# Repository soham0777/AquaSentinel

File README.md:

<div align="center">

**[Website](https://soham0777.github.io/AquaSentinel/)** · **[Live dashboard](https://aquasentinel-live.web.app)** · **[Pitch film](docs/media/aquasentinel-pitch-film.mp4)** · **[Journey film](docs/media/aquasentinel-journey-film.mp4)** · **[Finale deck](01_PITCH_20Nov/02_Pitch_Deck_7min_AS_SUBMITTED_17Nov.pdf)** · **[Drawings](04_R3_FULL_SIZE_DESIGN/04_Drawings/AquaSentinel_R3_Drawing_Set.pdf)** · **[Cost sheet](08_COST_AND_BUSINESS/04_AquaSentinel_Cost_48k_Value_Engineered.pdf)**

</div>

---

## 🏆 Encouragement Award, AAKRUTI 2026 India Finale

On **20 November 2026**, at the India Finale of the 16th **AAKRUTI Innovation Competition** by **Dassault Systèmes** (DS Campus, Pune), **AquaSentinel received an Encouragement Award**. The competition drew more than 15,000 students in 2,443 teams. **Sanjivani University** also received an **Outstanding College Participation** award.

<p align="center">

<br><sub>Left: our team presenting AquaSentinel at the India Finale. Right: finalists, jury and organisers. Photos: Dassault Systèmes Solutions Lab, from <a href="https://www.linkedin.com/posts/aakrutiinnovationcompetition2026-3dexperienceworld2027-ugcPost-7529524580290416640-ub56/">the official results post</a>.</sub>
</p>

> 🌟 **Encouragement Awards:** Sanjivani's Hero, **AquaSentinel**, SANJIVANI UNIVERSITY
> <br><sub>From the organisers' results post, <a href="https://www.linkedin.com/posts/aakrutiinnovationcompetition2026-3dexperienceworld2027-ugcPost-7529524580290416640-ub56/">Dassault Systèmes Solutions Lab on LinkedIn</a>. Also reported by <a href="https://www.punekarnews.in/indian-students-win-dassault-systemes-aakruti-2026-with-healthcare-innovations/">Punekar News</a>, 20 Nov 2026.</sub>

Jury: Lalit Kumar Das, Sudhir Patil, Aditi Singh, Ravikiran Pothukuchi and Suchit Jain.

---

## The problem, in four numbers

| | |
|---:|---|
| **1.4 million** | people die every year from unsafe drinking water, sanitation and hygiene (WHO, 2023) |
| **2 lakh** | Indians die every year for lack of safe water (NITI Aayog, 2018) |
| **296** | polluted river stretches and locations in India; **54** in Maharashtra, the most of any state (CPCB, 2025) |
| **once a month** | how often most river monitoring points are sampled, by hand. A spill lasts a few hours. |

On the Godavari at Kopargaon, a spill at two in the morning looks like water. By sunrise it has moved on, and nobody was there to take the sample.

## Our answer

> **AquaSentinel rides a guide pole on a bridge pier, reads the water every 15 minutes, and when the river changes it lights a red beacon, raises an SMS alert and bottles a sample of that water, at that minute, for the lab.**

```mermaid
flowchart LR
    R(["River"]) --> S["7 sensors<br/>pH · TDS · turbidity · water temp<br/>air temp + humidity · light · MQ-3"]
    S --> N["Arduino Nano<br/>on our milled Sensor Hub"]
    N -- "USB · one line a second" --> P["Raspberry Pi<br/>141 lines of decision rules"]
    P --> B{"Normal for<br/>this river?"}
    B -- yes --> L["Log · green light"]
    B -- "2 of 3 readings unusual" --> A["Red beacon · SMS alert<br/>pump fills the sample bottle"]
```

## Watch it

<table>
<tr>
<td width="50%" align="center"><br><b>The pitch</b> · 92 s<br><sub>The problem, the float, how it works and what it costs.</sub></td>
<td width="50%" align="center"><br><b>Our journey</b> · 92 s<br><sub>From our first handwritten page to the board we milled, and what we learned.</sub></td>
</tr>
</table>

<sub>Both films are made only from our own CAD, renders, drawings, dashboard captures and sourced figures. The milling shot is drawn from our real isolation G-code.</sub>

## Pour something in

The 1:5 LIVE model on our table carries the real, full-size sensors in a dish of water. Change the water and it names what it sees.

| Put this in the dish | It says | Because |
|---|---|---|
| Clean tap water | 🟢 **NORMAL** | readings stay where it learned them |
| A spoon of salt | 🔴 **INDUSTRIAL** | dissolved solids jump |
| A little vinegar | 🔴 **ACIDIC** | pH falls |
| A spoon of soil | 🔴 **RUNOFF** | the water turns cloudy while the salts stay flat |
| Sanitiser held at the bottle | 🔴 **SOLVENT** | vapour above the sample |
| Pull out the temperature probe | 🔴 **SENSOR FAULT** (blinking) | a dead sensor is never reported as clean water |

It learns the dish for 20 seconds first, and needs two unusual readings out of three before it calls anything.

<p align="center"><br><sub>The Raspberry Pi's dashboard after a spoon of salt, captured from the simulator built into our software.</sub></p>

## The board we milled

- **Why:** ten small boards on a tray clashed twice in SOLIDWORKS, so we drew one board instead.
- **What:** Sensor Hub v1.2, 104 × 72 mm, single-sided, drawn in KiCad, milled on a desktop CNC on **12 November**.
- **How:** an Arduino Nano reads all seven sensors and drives the light and the pump; every sensor has its own labelled header.
- **Learned:** Windows blocked the usual milling program, so we wrote our own G-code sender. The TDS board disturbs the pH probe, so the Nano powers it only while it reads.
- **Tested:** on **13 November** all seven sensors, the beacon and the pump answered through the board.

<br clear="right">

## The full-size float, R3

<p align="center"> <br><sub>Left: the R3 at dusk, rendered in 3DEXCITE Creative Experience on the 3DEXPERIENCE platform. Right: the float follows the river through 2 m of rise.</sub></p>

| | |
|---|---|
| **Assembly** | 66 part numbers, 144 parts, 48.5 kg, one SOLIDWORKS assembly |
| **Structure** | 316L pole and pier brackets, 6061 aluminium frame, rotomoulded PE hulls |
| **Motion** | rides a 2-inch pole on eight rollers through 2 m of river rise; turns with the current like a weathervane |
| **Design checks** | **14 of 14 pass**: reserve buoyancy 2.27, freeboard 143 mm, righting arm positive to 60° |
| **Guide pole** | 64.0 MPa with pinned ends and the carriage couple: safety factor **2.66** on 170 MPa |
| **CAD caught** | the pole running through the electronics pod, and a mass of 48.5 kg, not the 25.4 kg we guessed |

### Six SOLIDWORKS drawings

<p align="center">  <br><sub>AS3-DWG-01 to 06, A3, first-angle: installation, float, guide carriage, sensor well, hull, pier bracket. Native <code>.SLDDRW</code> files in <a href="04_R3_FULL_SIZE_DESIGN/04_Drawings/SOLIDWORKS">04_Drawings/SOLIDWORKS</a>.</sub></p>

## How we got here

```mermaid
timeline
    title AquaSentinel, 2026
    Idea : One page of ideas, called AquaRight then
    Design : The R3 in SOLIDWORKS : CAD stops us twice
    5 Oct : FDC submitted : pole and bracket simulated
    31 Oct : 1:5 LIVE model designed around the real sensors
    7 Nov : Assembly manuals
    12 Nov : Sensor Hub milled with our own G-code sender
    13 Nov : All seven sensors answer through the board
    19–20 Nov : India Geo Finale, DS Campus, Pune : Encouragement Award
```

## What it costs

| | |
|---|---|
| One sentinel at 100 units | **₹47,886** before GST |
| The first one | ₹64,616 |
| One real-time monitoring station | ₹35–40 lakh, the price of **73–84** sentinels |
| Proposed service | ₹8,000 a month; hardware paid back in about 12 months |

Costed from Indian supplier listings, November 2026, line by line in [the cost sheet](08_COST_AND_BUSINESS/04_AquaSentinel_Cost_48k_Value_Engineered.pdf).

## Run the software, no hardware needed

```bash
cd 07_RASPBERRY_PI_SOFTWARE/aquasentinel
python3 -m aquasentinel --simulate     # dashboard on http://localhost:8080, plays the six waters
python3 tools/self_test.py             # checks the decision rules on every water
```

On the Raspberry Pi, `bash install.sh` sets up the service, the SIM800L port and the full-screen dashboard. See [PI_SETUP_AND_OPERATION.md](07_RASPBERRY_PI_SOFTWARE/aquasentinel/PI_SETUP_AND_OPERATION.md).

## Inside this repository

| Folder | What you will find |
|---|---|
| [`01_PITCH_20Nov`](01_PITCH_20Nov) | the 7-minute finale deck (PPTX + PDF), the final pitch script, a one-page glance card, the mechanical and design Q&A, and the fact check behind every number |
| [`02_FILMS`](02_FILMS) | the pitch film and the journey film (both have music), and the team's raw recordings |
| [`03_BOOTH_PRINTS`](03_BOOTH_PRINTS) | every booth print: A1 poster, 12 A3 story boards, drawings, leave-behind, part tags, "Try me" stickers, bottle labels, with the print order sheet |
| [`04_R3_FULL_SIZE_DESIGN`](04_R3_FULL_SIZE_DESIGN) | R3 assembly manual, parts list, Pack and Go, native SOLIDWORKS parts, six drawings, 14 design checks, renders, STEP for every part, and the pole and bracket FEA |
| [`05_LIVE_MODEL_1to5`](05_LIVE_MODEL_1to5) | the 1:5 LIVE model: 31-page assembly manual, 38 STL print files, SOLIDWORKS parts and assembly |
| [`06_ELECTRONICS_AND_PCB`](06_ELECTRONICS_AND_PCB) | electronics manual, Sensor Hub v1.2 KiCad design, G-code, our G-code sender, Nano firmware |
| [`07_RASPBERRY_PI_SOFTWARE`](07_RASPBERRY_PI_SOFTWARE) | decision rules, dashboard, SMS, Firebase cloud, logging, installer, self-test |
| [`08_COST_AND_BUSINESS`](08_COST_AND_BUSINESS) | the cost summary, the full working and the cost sheet |
| [`09_CREATIVE_EXPERIENCE_3DEXCITE`](09_CREATIVE_EXPERIENCE_3DEXCITE) | 3DEXCITE storyline, assets and renders, AR model, story video |
| [`10_SUBMISSIONS_AND_CERTIFICATES`](10_SUBMISSIONS_AND_CERTIFICATES) | every stage we submitted, the FDC report and the participation certificates |
| [`11_PROJECT_RECORDS_AND_AUDITS`](11_PROJECT_RECORDS_AND_AUDITS) | audits, reorganisation and purge reports, the backup policy |
| [`docs`](docs) | the project website, the films and every image on this page |

New here? Start with [`00_START_HERE.md`](00_START_HERE.md).

## Where it stands

| Proven | Not yet |
|---|---|
| All 7 sensors, the beacon and the pump work through our own board (13 Nov) | an SMS received end to end |
| The Raspberry Pi reads the board live; pH, turbidity and MQ-3 calibrated | the 1:5 model floated in water |
| The [live cloud dashboard](https://aquasentinel-live.web.app) shows the Kopargaon 1:5 station (18 Nov) | the full-size R3 built: it is a design, checked in CAD |
| R3: 14 of 14 design checks, 2 SOLIDWORKS Simulation studies | a tank test, then 30 days on the Godavari |

## The team

**Built by**

| | |
|---|---|
| **Soham Prabhakar Kadu** | Team leader and project lead · Third Year, AI & ML |
| **Bhakti Ajay Kadam** | Electronics lead, finale presenter · Third Year, Computer Science & Engineering |

**Team Sanjivani Hero's Journey** also included Prasad Satish Ugale (Direct Second Year, Mechanical Engineering) and Tanmay Nilesh Pendbhaje (First Year, Mechanical Engineering), with Dr. Kiran Wakchaure as mentor.

AG26-1500$41 · Sanjivani University, Kopargaon · AAKRUTI Innovation Competition 2026 by Dassault Systèmes

<sub>Code and documentation are under the MIT licence; the presentation, films, renders and drawings are the team's copyright. Award photos are © Dassault Systèmes, shown with credit. See [LICENSE](LICENSE).</sub>

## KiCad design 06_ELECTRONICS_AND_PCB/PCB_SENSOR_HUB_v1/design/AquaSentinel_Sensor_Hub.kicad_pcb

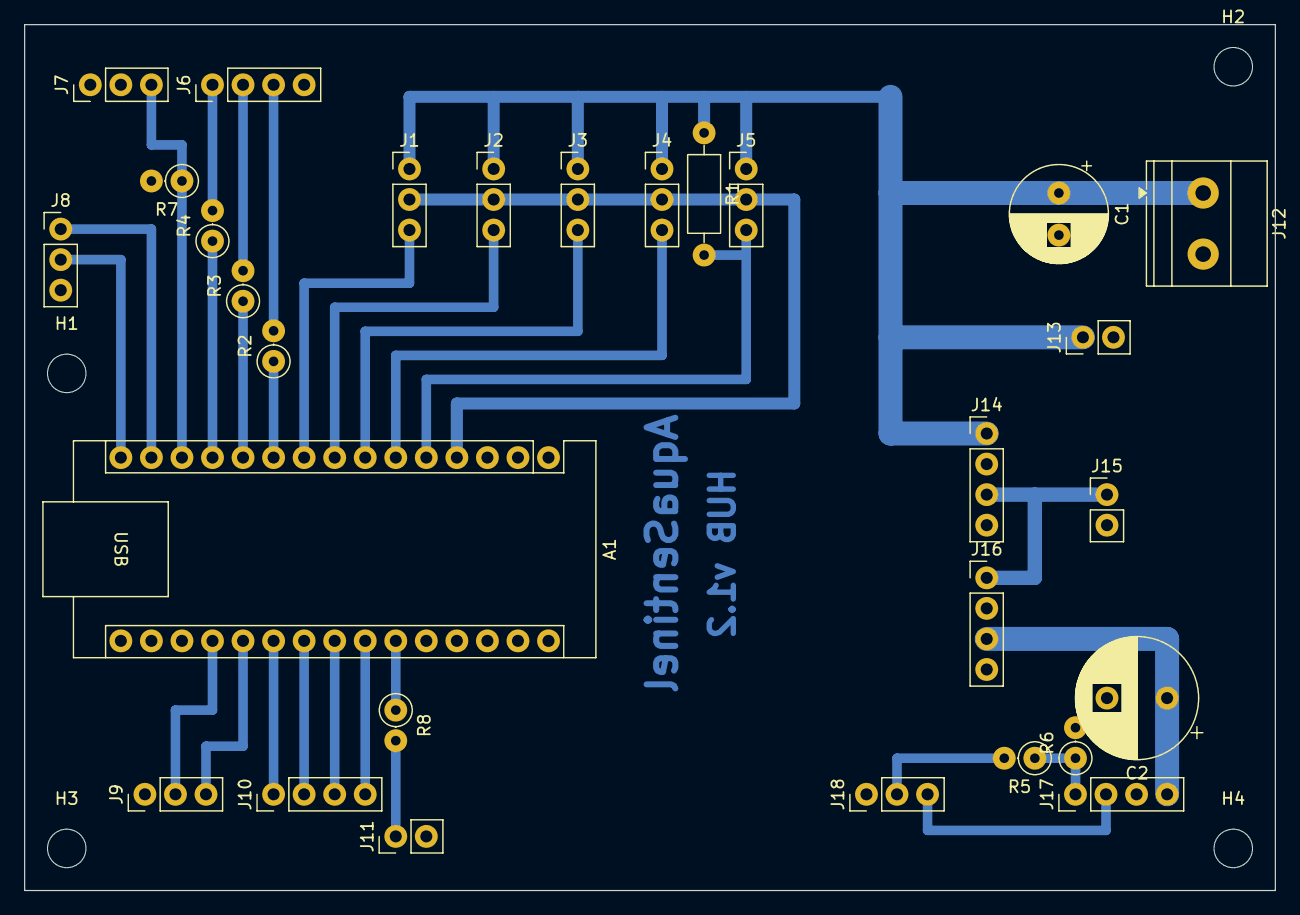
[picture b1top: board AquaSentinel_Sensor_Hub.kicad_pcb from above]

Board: 2 copper layers, 104.0 x 72.0 mm, 33 parts (0 on the bottom side), 29 nets.

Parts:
A1: Arduino Nano (socket); Arduino_Nano
C1: 470uF 16V; CP_Radial_D8.0mm_P3.50mm
C2: 1000uF 16V; CP_Radial_D10.0mm_P5.00mm
H1, H2, H3, H4: MountingHole_3.2mm_M3
J1: ALCOHOL MQ-3; PinHeader_1x03_P2.54mm_Vertical
J2: TURBIDITY; PinHeader_1x03_P2.54mm_Vertical
J3: LIGHT LDR; PinHeader_1x03_P2.54mm_Vertical
J4: AIR DHT11; PinHeader_1x03_P2.54mm_Vertical
J5: WATER TEMP DS18B20; PinHeader_1x03_P2.54mm_Vertical
J6: BEACON RGB (B R G -); PinHeader_1x04_P2.54mm_Vertical
J7: PUMP CTRL (GND IN2 IN1); PinHeader_1x03_P2.54mm_Vertical
J8: SPARE (D11 D12 GND); PinHeader_1x03_P2.54mm_Vertical
J9: TDS (GND PWR SIG); PinHeader_1x03_P2.54mm_Vertical
J10: ANALOG SPARE (A2 A3 A4 A5); PinHeader_1x04_P2.54mm_Vertical
J11: pH SIGNAL (O GND); PinHeader_1x02_P2.54mm_Vertical
J12: AUX 5V IN; TerminalBlock_Phoenix_MKDS-1,5-2-5.08_1x02_P5.08mm_Horizont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
J13: PUMP POWER (+ -); PinHeader_1x02_P2.54mm_Vertical
J14: STEP-UP 9V (IN+ IN- OUT+ OUT-); PinHeader_1x04_P2.54mm_Vertical
J15: pH POWER 9V (+ -); PinHeader_1x02_P2.54mm_Vertical
J16: STEP-DOWN 4.0V (IN+ IN- OUT+ OUT-); PinHeader_1x04_P2.54mm_Vertical
J17: SIM800L (RXD TXD GND VCC); PinHeader_1x04_P2.54mm_Vertical
J18: RASPBERRY PI (GND6 TX8 RX10); PinHeader_1x03_P2.54mm_Vertical
R1: 4.7k DS18B20 pull-up; R_Axial_DIN0207_L6.3mm_D2.5mm_P10.16mm_Horizontal
R2, R3, R4: 220R; R_Axial_DIN0207_L6.3mm_D2.5mm_P2.54mm_Vertical
R5: 4.7k; R_Axial_DIN0207_L6.3mm_D2.5mm_P2.54mm_Vertical
R6: 10k; R_Axial_DIN0207_L6.3mm_D2.5mm_P2.54mm_Vertical
R7: 10k pump pull-down; R_Axial_DIN0207_L6.3mm_D2.5mm_P2.54mm_Vertical
R8: 4.7k pH protect; R_Axial_DIN0207_L6.3mm_D2.5mm_P2.54mm_Vertical

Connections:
+4V0: C2.1, J16.3, J17.4
+5V_AUX: C1.1, J1.1, J2.1, J3.1, J4.1, J5.1, J12.1, J13.1, J14.1, R1.1
+9V: J14.3, J15.1, J16.1
A0_TDSPWR: A1.19, J9.2
A1_TDS: A1.20, J9.3
A2_SP: A1.21, J10.1
A3_SP: A1.22, J10.2
A4_SP: A1.23, J10.3
A5_SP: A1.24, J10.4
A6_PH: A1.25, R8.1
D2_TEMP: A1.5, J5.3, R1.2
D3_AIR: A1.6, J4.3
D4_LIGHT: A1.7, J3.3
D5_TURB: A1.8, J2.3
D6_ALC: A1.9, J1.3
D7_G: A1.10, R2.1
D7_G_LED: J6.3, R2.2
D8_R: A1.11, R3.1
D8_R_LED: J6.2, R3.2
D9_B: A1.12, R4.1
D9_B_LED: J6.1, R4.2
D10_PUMP: A1.13, J7.3, R7.1
D11_SP: A1.14, J8.1
D12_SP: A1.15, J8.2
GND: A1.4, A1.29, C1.2, C2.2, J1.2, J2.2, J3.2, J4.2, J5.2, J6.4, J7.1, J7.2, J8.3, J9.1, J11.2, J12.2, J13.2, J14.2, J14.4, J15.2, J16.2, J16.4, J17.3, J18.1, R6.2, R7.2
PH_IN: J11.1, R8.2
PI_TX: J18.2, R5.2
SIM_RXD: J17.1, R5.1, R6.1
SIM_TXD: J17.2, J18.3

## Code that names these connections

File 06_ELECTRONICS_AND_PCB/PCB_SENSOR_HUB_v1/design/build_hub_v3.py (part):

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track([('R1', 2), (60.0, 19.16)], 'D2_TEMP', SIG)

# ---------------- top-left: RGB beacon (standing 220R), pump control (+10k), spare ----------------
for ref, rnet, pin, y1 in (('R2', 'D7_G', 10, 28.0), ('R3', 'D8_R', 11, 23.0), ('R4', 'D9_B', 12, 18.0)):
    x = NX(pin)
    place('Resistor_THT', 'R_Axial_DIN0207_L6.3mm_D2.5mm_P2.54mm_Vertical', ref, '220R', x, y1, 0,
          {'1': rnet, '2': rnet + '_LED'})
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track([('A1', 19), (NX(19), 57.0), (12.54, 57.0), ('J9', 2)], 'A0_TDSPWR', SIG)
track([('A1', 20), (NX(20), 60.0), (15.08, 60.0), ('J9', 3)], 'A1_TDS', SIG)
hdr(4, 'J10', 'ANALOG SPARE (A2 A3 A4 A5)', NX(21), 64.0, 'right', {'1': 'A2_SP', '2': 'A3_SP', '3': 'A4_SP', '4': 'A5_SP'})
for pin, k, nn in ((21, 1, 'A2_SP'), (22, 2, 'A3_SP'), (23, 3, 'A4_SP'), (24, 4, 'A5_SP')):
    track([('A1', pin), ('J10', k)], nn, SIG)
place('Resistor_THT', 'R_Axial_DIN0207_L6.3mm_D2.5mm_P2.54mm_Vertical', 'R8', '4.7k pH protect', NX(25), 57.0, 0,
      {'1': 'A6_PH', '2': 'PH_IN'})
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

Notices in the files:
README.md:
License: MIT
